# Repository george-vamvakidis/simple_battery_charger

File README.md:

# simple_battery_charger
A simple battery charger made using the Zener diode properties.

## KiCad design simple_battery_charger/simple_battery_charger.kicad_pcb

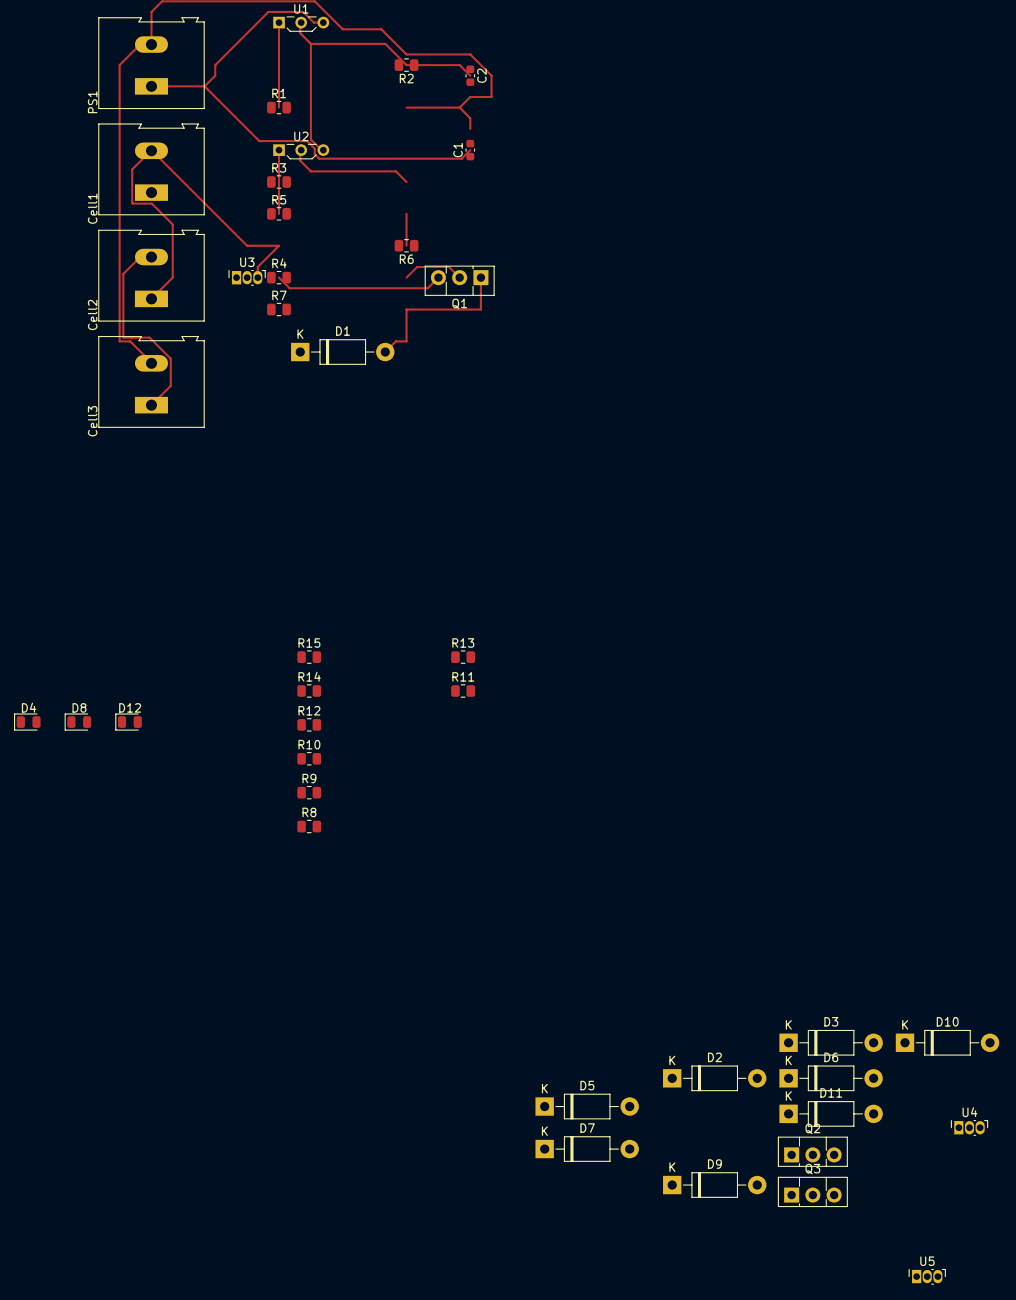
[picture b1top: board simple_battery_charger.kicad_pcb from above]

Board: 2 copper layers, 41 parts (0 on the bottom side), 26 nets.

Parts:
C1, C2: 100uF; C_0603_1608Metric
Cell1, Cell2, Cell3: Conn_01x02; TerminalBlock_Altech_AK300-2_P5.00mm
D1, D2, D3, D5, D6, D7, D9, D10, D11: 1N4007; D_DO-41_SOD81_P10.16mm_Horizontal
D4, D8, D12: LED GRN; LED_0805_2012Metric
PS1: Conn_01x02; TerminalBlock_Altech_AK300-2_P5.00mm
Q1, Q2, Q3: BD140; TO-126-3_Vertical
R1: 4.7k Ω; R_0805_2012Metric
R2: 517 Ω; R_0805_2012Metric
R3: 2 Ω; R_0805_2012Metric
R4, R8, R12: 1k Ω; R_0805_2012Metric
R5, R9, R13: 20.4k Ω; R_0805_2012Metric
R6, R10, R14: 30k Ω; R_0805_2012Metric
R7, R11, R15: 330 Ω; R_0805_2012Metric
U1, U2: LM317; Diodes_SIP-3_4.1x1.5mm_P2.65mm
U3, U4, U5: TL431D; Allegro_SIP-3

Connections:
+12V: Cell1.1, Q1.2 (C), R3.1, R4.2, R5.1, U2.1 (ADJ)
+24V: C1.1, PS1.1, U1.3 (VI)
/ADJ2R1: R1.1, R2.2, U1.1 (ADJ)
/CELL1_Out: Cell1.2, Cell2.1, D3.1 (K), D4.1 (K), Q2.2 (C), R6.2, R8.2, R9.1, U3.2 (A), U3.3 (A)
/CELL2_Out: Cell2.2, Cell3.1, D7.1 (K), D8.1 (K), Q3.2 (C), R10.2, R12.2, R13.1, U4.2 (A), U4.3 (A)
/R2toReg: C2.1, R2.1, U1.2 (VO), U2.3 (VI)
/VouttoR3: R3.2, U2.2 (VO)
GND: C1.2, C2.2, Cell3.2, D11.1 (K), D12.1 (K), PS1.2, R1.2, R14.2, U5.2 (A), U5.3 (A)
unnamed: D1.1 (K), D2.2 (A)
unnamed: D1.2 (A), Q1.1 (E), R7.2
unnamed: D2.1 (K), D3.2 (A)
unnamed: D4.2 (A), R7.1
unnamed: D5.1 (K), D6.2 (A)
unnamed: D5.2 (A), Q2.1 (E), R11.2
unnamed: D6.1 (K), D7.2 (A)
unnamed: D8.2 (A), R11.1
unnamed: D9.2 (A), Q3.1 (E), R15.2
unnamed: D10.1 (K), D11.2 (A)
unnamed: D9.1 (K), D10.2 (A)
unnamed: D12.2 (A), R15.1
unnamed: Q1.3 (B), R4.1, U3.1 (K)
unnamed: Q2.3 (B), R8.1, U4.1 (K)
unnamed: Q3.3 (B), R12.1, U5.1 (K)
unnamed: R5.2, R6.1
unnamed: R9.2, R10.1
unnamed: R13.2, R14.1
